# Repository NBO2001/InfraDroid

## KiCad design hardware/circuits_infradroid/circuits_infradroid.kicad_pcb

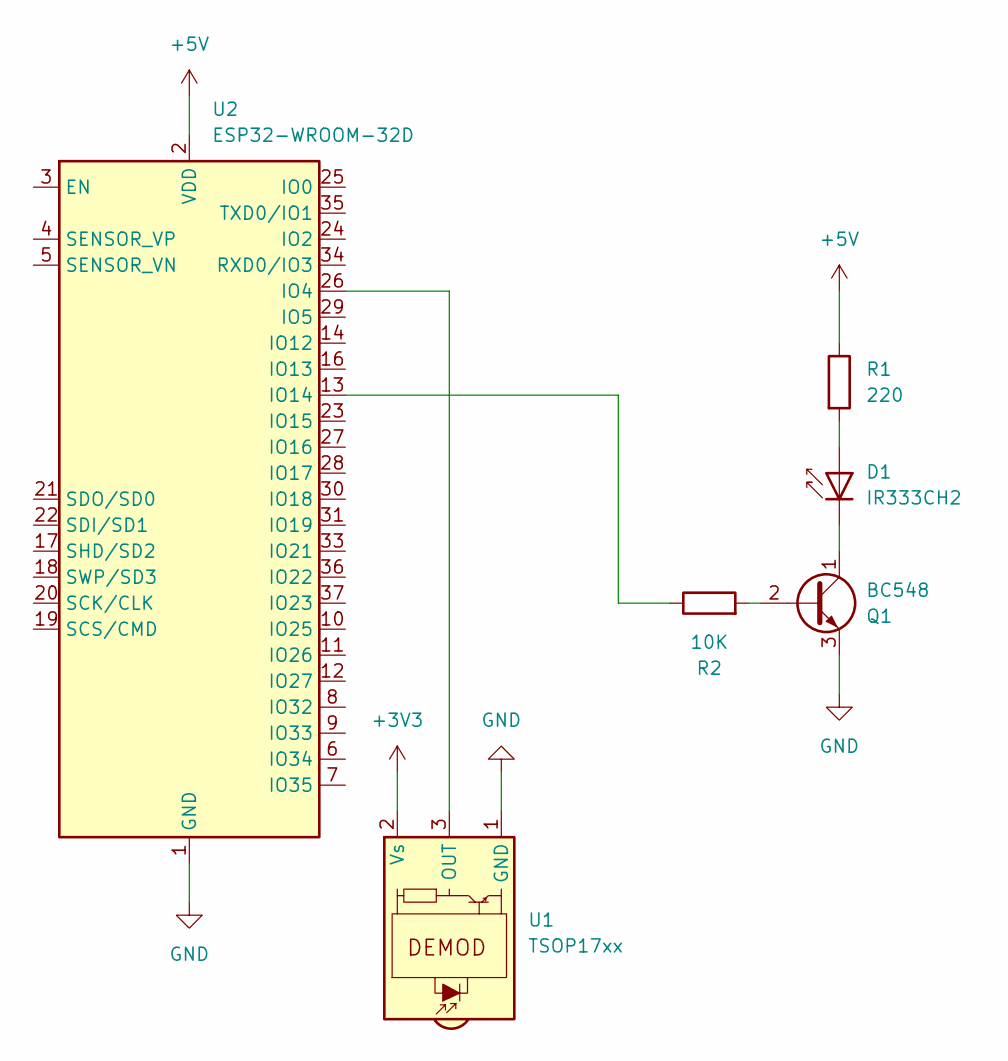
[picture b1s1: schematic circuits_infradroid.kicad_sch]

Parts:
D1: IR333CH2; LED_D5.0mm_IRGrey
Q1: BC548; TO-92_Inline
R1: 220; R_Axial_DIN0204_L3.6mm_D1.6mm_P1.90mm_Vertical
R2: 10K; R_Axial_DIN0204_L3.6mm_D1.6mm_P1.90mm_Vertical
U1: TSOP17xx; Vishay_CAST-3Pin
U2: ESP32-WROOM-32D; ESP32-WROOM-32E

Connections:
+3V3: U1.2 (Vs)
+5V: R1.1, U2.2 (VDD)
GND: Q1.3 (E), U1.1 (GND), U2.1 (GND), U2.15 (GND), U2.38 (GND), U2.39 (GND)
unnamed: D1.2 (A), R1.2
unnamed: D1.1 (K), Q1.1 (C)
unnamed: Q1.2 (B), R2.2
unnamed: U1.3 (OUT), U2.26 (IO4)
unnamed: R2.1, U2.13 (IO14)

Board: 2 copper layers, 6 parts (0 on the bottom side), 7 nets, no tracks yet.

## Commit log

2025-12-17 links e protocolos
2025-12-17 links e protolocos
2025-12-30 Preparação para criação do firmware / hardware
    Criação dos receiver e emitter
    Criação da identidade visual
    Criação da libs padrão
    Download da lins IRremote.hpp
2025-12-31 criacao do mockup do case / atualizacao specs motorola g100 / atualizacao logo
2026-01-02 Mapping da Fita Led / ajuste no firmware / video do primeiro teste
2026-01-06 teste no comando SEND / id visual
2026-01-08 criacao do prototipo no figma
2026-01-10 mapping do dados RAW do controle / tentativa (fail) de emitir sinal
2026-01-12 slides e outros
2026-01-15 testes no emissor OK! | registros do teste
2026-01-15 teste 2 de emissao OK / circuitos no kicad / registro em video do teste 2
2026-01-16 pasta kernel -> driver / definicao estava errada
2026-01-17 Testes e criacao do driver para linux
    Funcionamento ok, entrada de dados ainda em RAW... isso pode dificultar na hora de fazer a programacao, mas isso vai ter que ser discutido no grupo.
2026-01-20 projeto do case para moto g100
2026-01-22 preparacao da hal
2026-01-23 quase deu certo a hal... mas nao deu tempo de testar o hw
2026-01-23 guia ir hal
2026-01-27 compilando kernel
2026-01-28 tentando resolver a hal
2026-01-28 .step do case
2026-01-28 id visual + slide 2
2026-01-30 preparação do slide 2
2026-01-30 slide 2, falta: driver, hal, app e integracao
2026-01-31 adicionei animacao aplicativo
2026-01-31 ajustes no slide 2
2026-02-01 revisao final (ayrton) do slide 2
2026-02-15 video do case led
2026-02-26 registros e slide 3
